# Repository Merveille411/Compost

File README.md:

# Compost Connecté

## Sommaire
- [Introduction](#introduction)
- [Résulat et problèmes rencontrés](#résulat-et-problèmes-rencontrés)
- [Conclusion](#conclusion)
- [À propos des dossiers](#à-propos-des-dossiers)

## Introduction

L’objectif de notre projet était de rendre le compost de l'ENSEA connecté et autonome, qu'il puisse envoyer un message d'alerte si les différents paramètre ne sont pas conforme.   
Nous arrivons donc au cahier des charges suivant :    

FP1 : La référence du capteur de température est [SA56004AD](https://www.nxp.com/part/SA56004AD#/), il est à l’ENSEA. Il lui faut une tension entre 3,3 et 5 V et un courant de 100 microA. [Datasheet](https://www.nxp.com/docs/en/brochure/75015962.pdf)    
FP2 : La référence du capteur d’acidité est [32638](https://www.gotronic.fr/art-sonde-ph-interface-sen0161-21552.htm), il n’est pas à l’ENSEA, il coûte 32,30€. Il lui faut une tension de 5V. [Datasheet](https://wiki.dfrobot.com/PH_meter_SKU__SEN0161_)    
FP3 : La référence du capteur d’humidité est [893-7082](https://fr.rs-online.com/web/p/capteurs-de-temperature-et-d-humidite/8937082), il n’est pas à l’ENSEA, il coûte 11,26€. Il lui faut une tension de 5V et un courant de 1,5 mA. [Datasheet](https://www.te.com/commerce/DocumentDelivery/DDEController?Action=showdoc&DocId=Data+Sheet%7FHPC052_J%7FA%7Fpdf%7FEnglish%7FENG_DS_HPC052_J_A.pdf%7FCAT-HSC0006)  
FP6 : La référence de l’écran est [4440](https://www.adafruit.com/product/4440), il est à l’ENSEA. Il lui faut une tension entre 3,3 et 5 V et un courant de 90 mA. [Datasheet](https://cdn-learn.adafruit.com/downloads/pdf/monochrome-oled-breakouts.pdf)   
    
Puisque nous avons deux capteurs et l'écran en connection I2C et le LoRa en connection UART, nous utiliserons un microprocesseur [STM32L412KBT6](https://www.digikey.fr/fr/products/detail/stmicroelectronics/STM32L412KBT6/9656219). Il est a l'ENSEA; [Datasheet](https://www.st.com/resource/en/datasheet/stm32l412kb.pdf)   
    
Le projet avancera d'après le planning prévisionnel suivant :

Les interactions entre les différents composants ainsi que la structure de base du projet est illustré de la manière suivante :

## Résulat et problèmes rencontrés

Globalement, pour tout les PCB, le fichier contraintes a été respecté sauf pour celui du capteur de température. Donc notre PCB est inutilisable.               
Sur le PCB du compost, on a fait des erreurs sur les pin utilisés par le microprocesseur. Ducoup, on ne peut pas connecté le module LoRa et les capteur en I2C en même temps.

Comme on peut le voir, le pA10 et pA9 permettent soit de faire la connection en UART ou en I2C tandis que pA4 et pA5 ne permet ne permet pas la connection en I2C comme prévu et il aurait fallu donc utilisé les pin pB6 et pB7.
                
Malgré ça, le PCB du compost et du capteur d'humidité ont leurs composants soudé parfaitement, sans erreur et les valeurs entre chaque point sont juste.               

De plus, le PCB du compost, qui contient le microprosseur a pu être flashé et donc il est prêt à être coder et à l'utilisation.         

## Conclusion   
        
Pour conclure, il nous restez plus qu'à faire le code des différents composants et de réunir l’ensemble des parties pour faire un test global. Il faudrait aussi corriger les choix des pin sur le schéma du PCB du compost afin d'avoir la connection en I2C et UART. Ce projet nous a permis d'avoir une meilleur prise en main sur des logiciels du type EAGLE ou STM32CubeIDE. Nous avons également appris à s'attribuer des tâches de manière efficace, à communiquer et de se fixer des objectifs tout le long du projet.

## À propos des dossiers
**EAGLE/**    
                
  &emsp; &emsp;  **DRU/**    
  &emsp; &emsp;  Ce dossier contient le fichier contraintes utiliser pour les différents PCB du projet    
  &emsp; &emsp; `ENSEA_2022_04_08.dru`: Le fichier contrainte de l'ensea                
                
  &emsp; &emsp;  **Libraries/**    
  &emsp; &emsp;  Ce dossier contient tout les libraries des composants utiliser dans ce projet    
  &emsp; &emsp; `c1.lbr`: La librarie d'un condensateur de 470 uF utilisé dans le PCB de l'alimentation     
  &emsp; &emsp; `c2.lbr`: La librarie d'un condensateur de 100 uF utilisé dans le PCB de l'alimentation     
  &emsp; &emsp; `c3.lbr`: La librarie d'un condensateur de 470 pF utilisé dans le PCB de l'alimentation      
  &emsp; &emsp; `CapteurHumidite.lbr`: La librarie du capteur d'humidité     
  &emsp; &emsp; `CapteurTemperature.lbr`: La librarie du capteur de température     
  &emsp; &emsp; `cin.lbr`: La librarie d'un condensateur de 10 uF utilisé dans le PCB de l'alimentation ainsi que dans le PCB complet du compost      
  &emsp; &emsp; `cout.lbr`: La librarie d'un condensateur de 22 uF utilisé dans le PCB de l'alimentation ainsi que dans le PCB complet du compost      
  &emsp; &emsp; `l.lbr`: La librarie d'une bobine de 220 uH utilisé dans le PCB de l'alimentation     
  &emsp; &emsp; `MC34063A.lbr`: La librarie du régulateur à découpage utilisé dans le PCB de l'alimentation    
  &emsp; &emsp; `RegLineaire.lbr`: La librarie du régulateur linéaire utilisé dans le PCB de l'alimentation ainsi que dans le PCB complet du compost     
  &emsp; &emsp; `STM32_librairy.lbr`: La librarie du microproccesseur le PCB complet du compost          
                
  &emsp; &emsp;  **PCB/**   
  &emsp; &emsp;  Ce fichier contient tout les schémas et les boards des composants utiliser dans ce projet   
                
  &emsp; &emsp; `Alimentation.sch`: Le schéma du PCB de l'alimentation        

  &emsp; &emsp; `Alimentation.brd`: Le board du PCB de l'alimentation    

  &emsp; &emsp; `CapteurHumidite.sch`: Le schéma du PCB du capteur d'humidité  

  &emsp; &emsp; `CapteurHumidite.brd`: Le board du PCB du capteur d'humidité    

  &emsp; &emsp; `CapteurTemperature.sch`: Le schéma du PCB du capteur dde température  

  &emsp; &emsp; `CapteurTemperature.brd`: Le board du PCB du capteur de température     

  &emsp; &emsp; `PCBCompost.sch`:  Le schéma du PCB complet du compost  

  &emsp; &emsp; `PCBCompost.brd`:  Le board du PCB complet du compost  

**Code/**               
                
&emsp; &emsp; Ce dossier contient le seul code qu'on a fait, il manque manque le code principal du micropocesseur, le code pHmètre, du campteur de température et d'humidité.           
&emsp; &emsp; `Screen.cpp`: Le code de l'écran en c++

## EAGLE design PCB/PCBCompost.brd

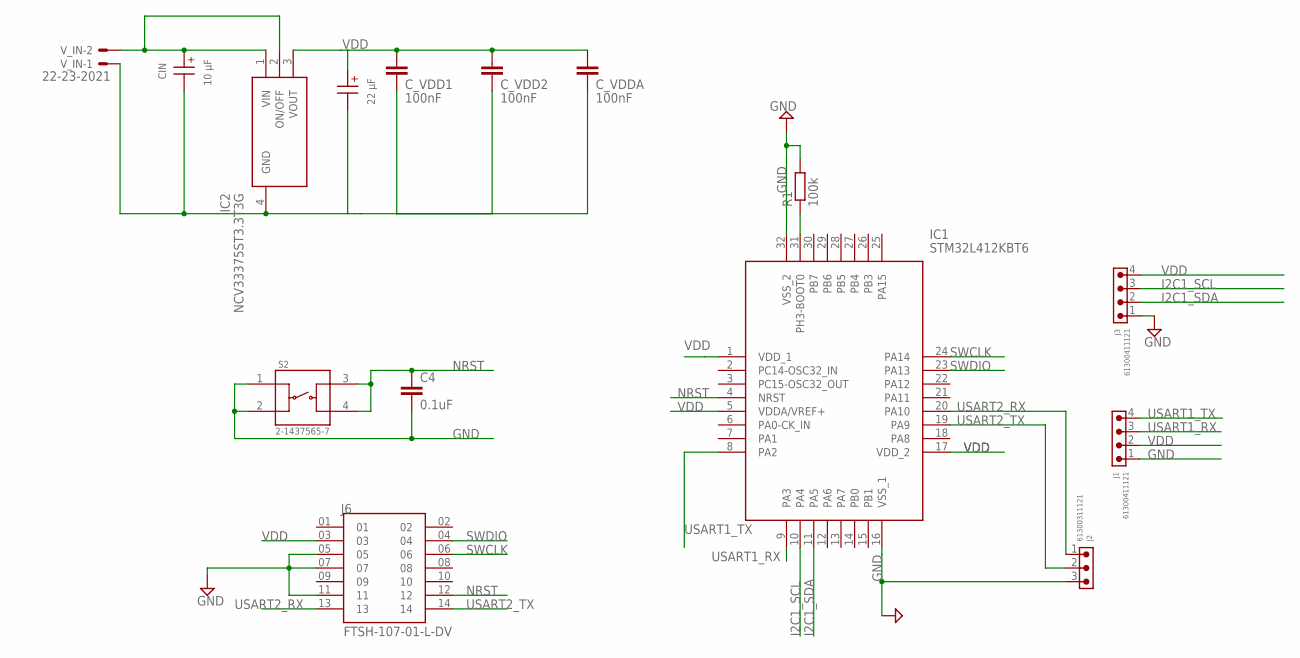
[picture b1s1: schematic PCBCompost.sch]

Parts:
C4: 0.1uF; C0603
CIN: 10 µF; WCAP-ASLL_4X5.5(DXL)
COUT: 22 µF; WCAP-ASLL_5X5.5(DXL)
C_VDD1, C_VDD2: 100nF; C0603
C_VDDA: 100nF; C0603
IC1: STM32L412KBT6; QFP80P900X900X160-32N
IC2: NCV33375ST3.3T3G; SOT230P700X175-4N
J1, J3: 61300411121
J2: 61300311121
J6: FTSH-107-01-L-DV; SAMTEC_FTSH-107-01-L-DV
R1: 100k; R0603
S2: 2-1437565-7; SW_2-1437565-7
V_IN: 22-23-2021

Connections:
GND: C4.2, CIN.2 (-), COUT.2 (-), C_VDD1.2, C_VDD2.2, C_VDDA.2, IC1.16 (VSS_1), IC1.32 (VSS_2), IC2.4 (GND), J1.1, J2.3, J3.1, J6.05, J6.07, J6.11, R1.2, S2.1, S2.2, V_IN.1
I2C1_SCL: IC1.10 (PA4), J3.3
I2C1_SDA: IC1.11 (PA5), J3.2
unnamed: IC1.31 (PH3-BOOT0), R1.1
unnamed: CIN.1 (+), IC2.1 (VIN), IC2.2 (ON/OFF), V_IN.2
NRST: C4.1, IC1.4 (NRST), J6.12, S2.3, S2.4
SWCLK: IC1.24 (PA14), J6.06
SWDIO: IC1.23 (PA13), J6.04
USART1_RX: IC1.9 (PA3), J1.3
USART1_TX: IC1.8 (PA2), J1.4
USART2_RX: IC1.20 (PA10), J2.1, J6.13
USART2_TX: IC1.19 (PA9), J2.2, J6.14
VDD: COUT.1 (+), C_VDD1.1, C_VDD2.1, C_VDDA.1, IC1.1 (VDD_1), IC1.5 (VDDA/VREF+), IC1.17 (VDD_2), IC2.3 (VOUT), J1.2, J3.4, J6.03

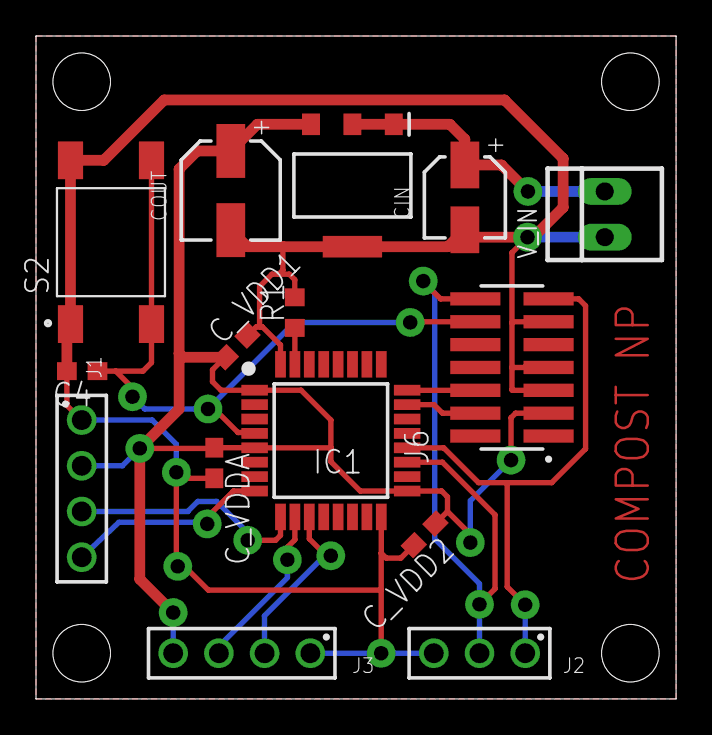
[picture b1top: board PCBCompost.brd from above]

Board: 2 copper layers, 35.6 x 36.8 mm, 15 parts (0 on the bottom side), 13 nets.

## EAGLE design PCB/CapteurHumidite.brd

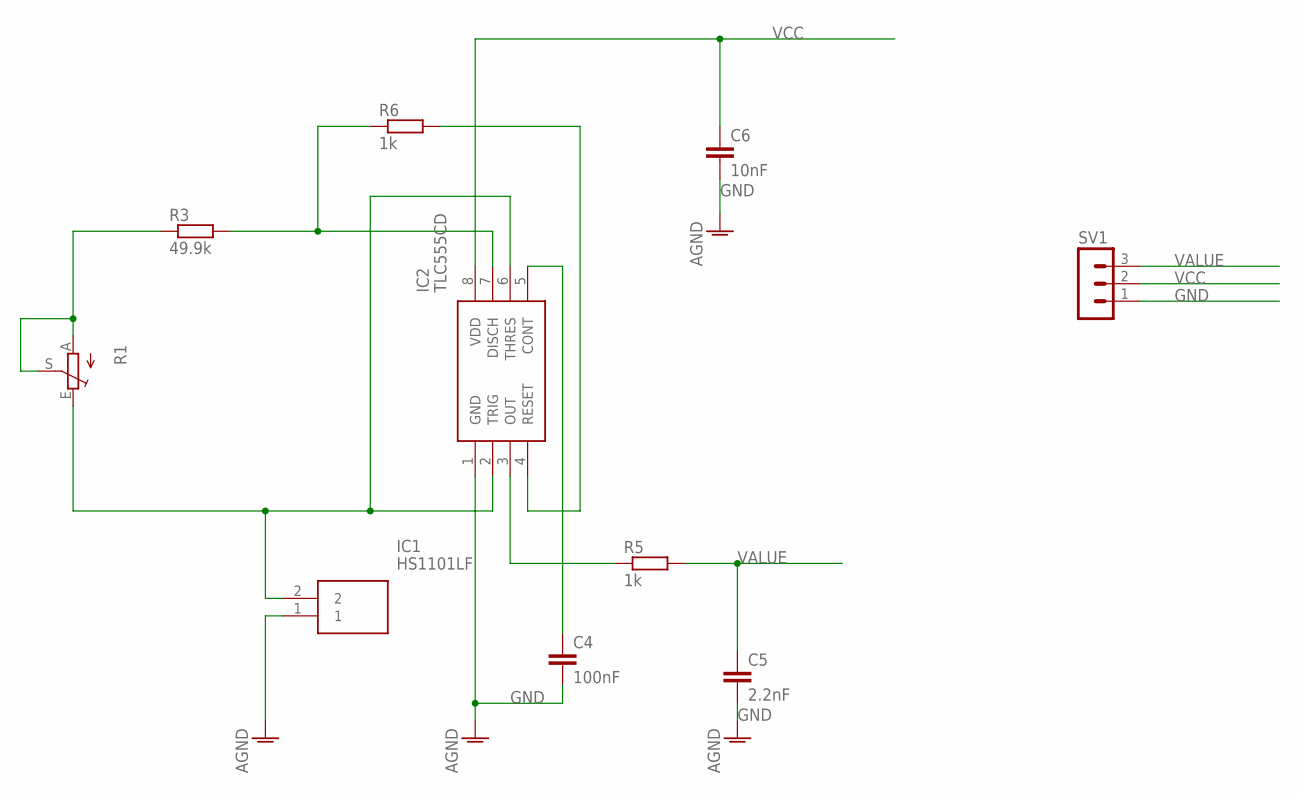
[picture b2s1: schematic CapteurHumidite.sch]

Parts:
C4: 100nF; C0603
C5: 2.2nF; C0603
C6: 10nF; C0603
IC1: HS1101LF
IC2: TLC555CD; SOIC127P600X175-8N
R1: TRIM_EU-B25P; B25P
R3: 49.9k; R0603
R5, R6: 1k; R0603
SV1: MA03-1

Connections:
GND: C4.2, C5.2, C6.2, IC1.1, IC2.1 (GND), SV1.1
unnamed: IC2.7 (DISCH), R3.2, R6.1
unnamed: IC2.4 (RESET), R6.2
unnamed: R1.A, R1.S, R3.1
unnamed: C4.1, IC2.5 (CONT)
unnamed: IC2.3 (OUT), R5.1
unnamed: IC1.2, IC2.2 (TRIG), IC2.6 (THRES), R1.E
VALUE: C5.1, R5.2, SV1.3
VCC: C6.1, IC2.8 (VDD), SV1.2

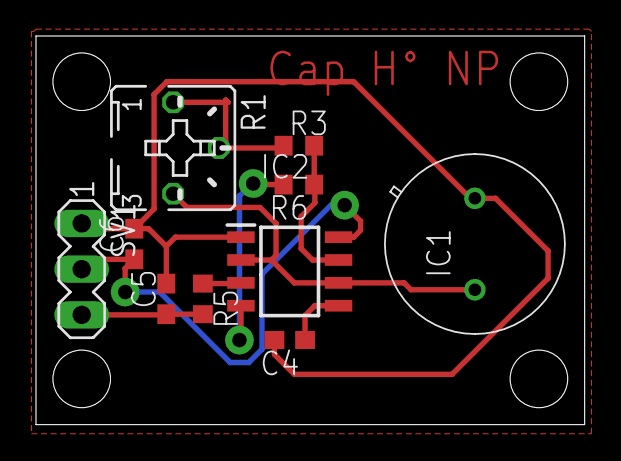
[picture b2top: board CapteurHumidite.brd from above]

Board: 2 copper layers, 30.5 x 21.6 mm, 10 parts (0 on the bottom side), 9 nets.

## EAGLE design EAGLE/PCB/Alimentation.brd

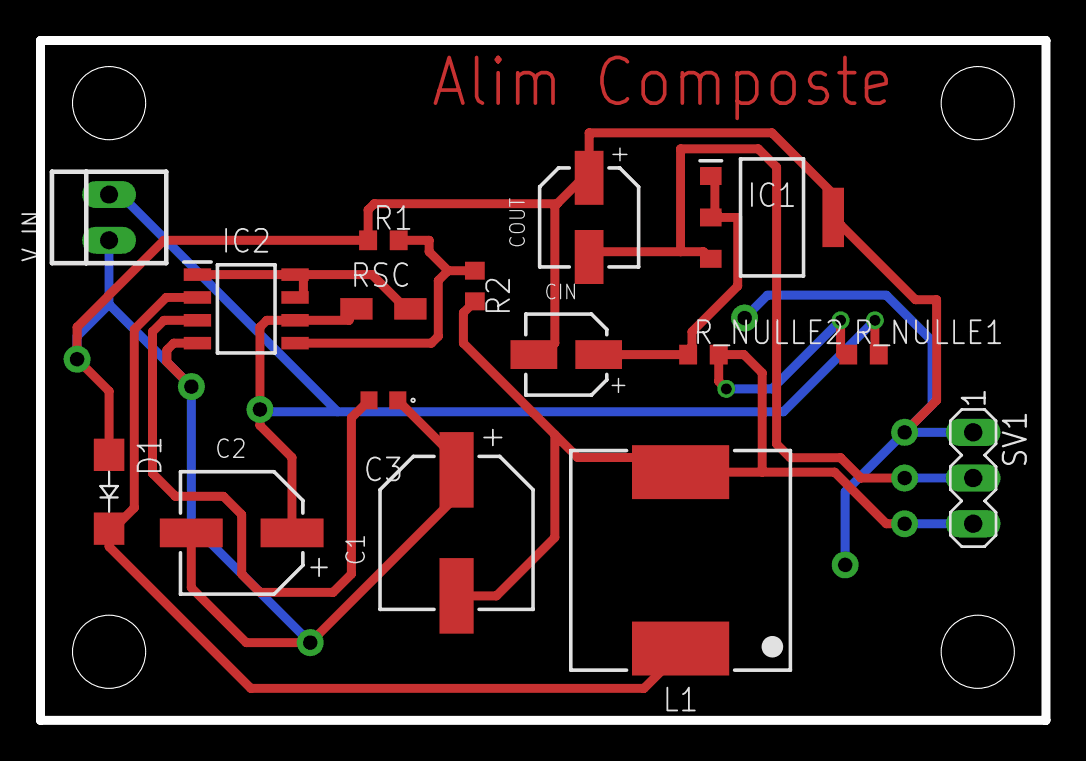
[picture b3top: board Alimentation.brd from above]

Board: 2 copper layers, 55.9 x 37.8 mm, 16 parts (0 on the bottom side), 9 nets.

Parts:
C1: 470 µF; WCAP-ASLL_8X10.5(DXL)
C2: 100 µF; WCAP-ASLL_6.3X7.7(DXL)
C3: C0603C471J5GACTU; C0603
CIN: 10 µF; WCAP-ASLL_4X5.5(DXL)
COUT: 22 µF; WCAP-ASLL_5X5.5(DXL)
D1: GF1; SMA-DO214AC
IC1: NCV33375ST3.3T3G; SOT230P700X175-4N
IC2: MC34063ACD-TR; SOIC127P600X175-8N
L1: 220uH; WE-PDA_1260
R1: 1.2k; R0603
R2: 3.6k; R0603
RSC: 0.3; R1206W
R_NULLE1, R_NULLE2: 0; R0603
SV1: MA03-1
V_IN: 22-23-2021

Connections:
GND: C1.1, C2.2, C3.1, CIN.2, COUT.1, D1.A, IC1.4, IC2.4, R1.1, SV1.1, V_IN.1
unnamed: IC2.5, R1.2, R2.1
unnamed: IC2.1, IC2.7, IC2.8, RSC.2
unnamed: C2.1, IC2.6, RSC.1, R_NULLE1.2, V_IN.2
unnamed: D1.K, IC2.2, L1.1
unnamed: C3.2, IC2.3
unnamed: CIN.1, IC1.1, IC1.2, R_NULLE2.1
VCC_3V: COUT.2, IC1.3, SV1.2
VCC_5V: C1.2, L1.2, R2.2, R_NULLE1.1, R_NULLE2.2, SV1.3

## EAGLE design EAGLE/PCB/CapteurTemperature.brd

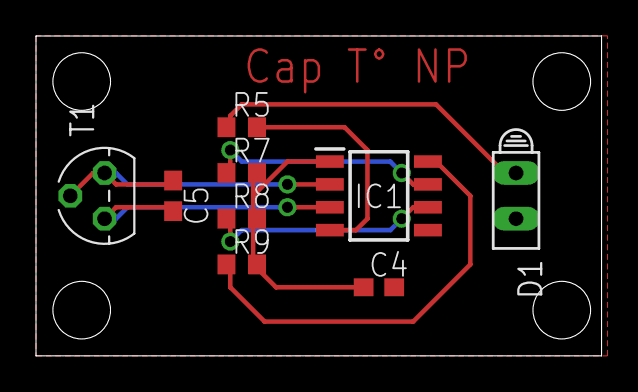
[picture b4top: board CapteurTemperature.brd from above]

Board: 2 copper layers, 31.4 x 17.8 mm, 9 parts (0 on the bottom side), 9 nets.

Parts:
C4, C5: C0603
D1: HLMP6
IC1: SOIC127P600X175-8N
R5, R7, R8, R9: R0603
T1: 2N3904; TO92

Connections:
GND: C4.2, D1.K, IC1.5
unnamed: C4.1, IC1.1, R7.2, R8.2, R9.2
unnamed: IC1.6, R8.1
unnamed: IC1.7, R7.1
unnamed: IC1.8, R9.1
unnamed: C5.1, IC1.2, T1.1, T1.2
unnamed: C5.2, IC1.3, T1.3
unnamed: IC1.4, R5.2
unnamed: D1.A, R5.1

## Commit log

2022-05-31 Create PCB
2022-05-31 Create Code

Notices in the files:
parts and their libraries:
c1: Copyright: Würth Elektronik
